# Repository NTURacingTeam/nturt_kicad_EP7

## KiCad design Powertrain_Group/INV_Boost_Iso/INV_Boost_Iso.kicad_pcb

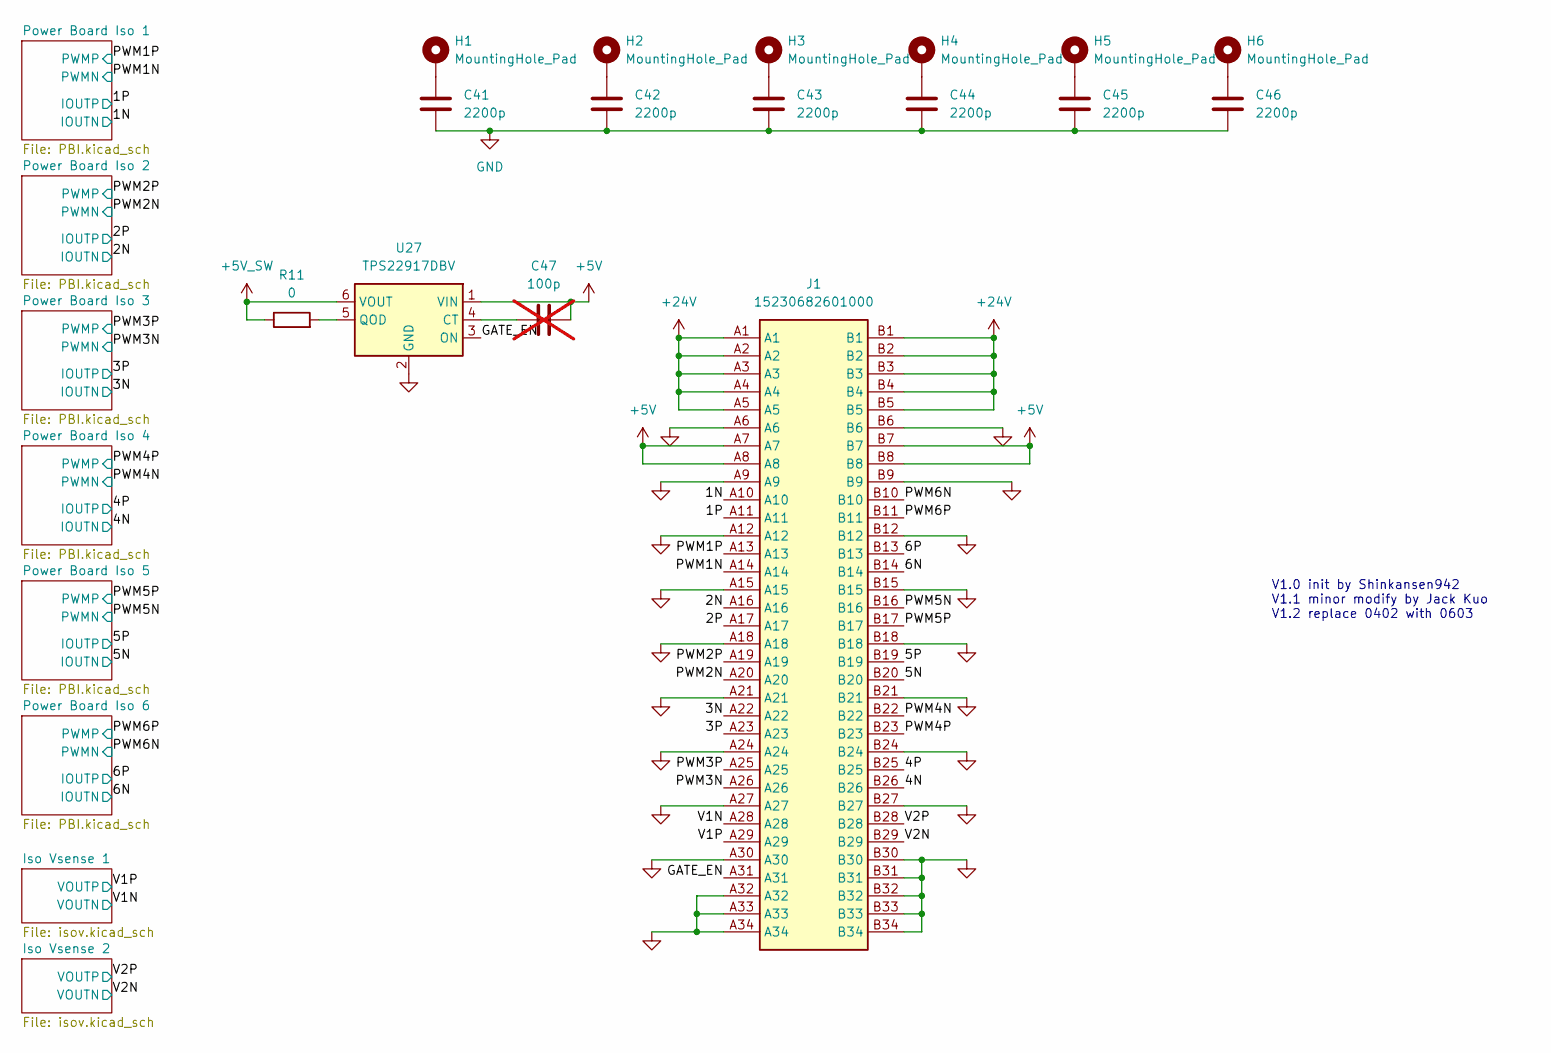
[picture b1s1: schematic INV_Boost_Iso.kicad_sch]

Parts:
C41, C42, C43, C44, C45, C46: 2200p; C_8060_Murata_DK1
C47: 100p; C_0402_1005Metric; not fitted
H1, H2, H3, H4, H5, H6: MountingHole_Pad; MountingHole_4.3mm_M4_Pad_Via
J1: 15230682601000; HARTING 15230682601000; Manufacturer_Part_Number 15230682601000; Mouser Part Number 617-15230682601000
R11: 0; R_0402_1005Metric
U27: TPS22917DBV; SOT-23-6

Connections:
+5V: C47.2, J1.A7, J1.A8, J1.B7, J1.B8, U27.1 (VIN); also elsewhere on the board
+5V_SW: R11.1, U27.6 (VOUT); also elsewhere on the board
+24V: J1.A1, J1.A2, J1.A3, J1.A4, J1.A5, J1.B1, J1.B2, J1.B3, J1.B4, J1.B5; also elsewhere on the board
/1N: J1.A10; also elsewhere on the board
/1P: J1.A11; also elsewhere on the board
/2N: J1.A16; also elsewhere on the board
/2P: J1.A17; also elsewhere on the board
/3N: J1.A22; also elsewhere on the board
/3P: J1.A23; also elsewhere on the board
/4N: J1.B26; also elsewhere on the board
/4P: J1.B25; also elsewhere on the board
/5N: J1.B20; also elsewhere on the board
/5P: J1.B19; also elsewhere on the board
/6N: J1.B14; also elsewhere on the board
/6P: J1.B13; also elsewhere on the board
/GATE_EN: J1.A31, U27.3 (ON)
/PWM1N: J1.A14; also elsewhere on the board
/PWM1P: J1.A13; also elsewhere on the board
/PWM2N: J1.A20; also elsewhere on the board
/PWM2P: J1.A19; also elsewhere on the board
/PWM3N: J1.A26; also elsewhere on the board
/PWM3P: J1.A25; also elsewhere on the board
/PWM4N: J1.B22; also elsewhere on the board
/PWM4P: J1.B23; also elsewhere on the board
/PWM5N: J1.B16; also elsewhere on the board
/PWM5P: J1.B17; also elsewhere on the board
/PWM6N: J1.B10; also elsewhere on the board
/PWM6P: J1.B11; also elsewhere on the board
/V1N: J1.A28; also elsewhere on the board
/V1P: J1.A29; also elsewhere on the board
/V2N: J1.B29; also elsewhere on the board
/V2P: J1.B28; also elsewhere on the board
GND: C41.1, C42.1, C43.1, C44.1, C45.1, C46.1, J1.A6, J1.A9, J1.A12, J1.A15, J1.A18, J1.A21, J1.A24, J1.A27, J1.A30, J1.A32, J1.A33, J1.A34, J1.B6, J1.B9, J1.B12, J1.B15, J1.B18, J1.B21, J1.B24, J1.B27, J1.B30, J1.B31, J1.B32, J1.B33, J1.B34, U27.2 (GND); also elsewhere on the board
unnamed: C41.2, H1.1
unnamed: C42.2, H2.1
unnamed: C43.2, H3.1
unnamed: C44.2, H4.1
unnamed: C45.2, H5.1
unnamed: C46.2, H6.1
unnamed: C47.1, U27.4 (CT)
unnamed: R11.2, U27.5 (QOD)

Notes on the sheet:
V1.0 init by Shinkansen942 V1.1 minor modify by Jack Kuo V1.2 replace 0402 with 0603

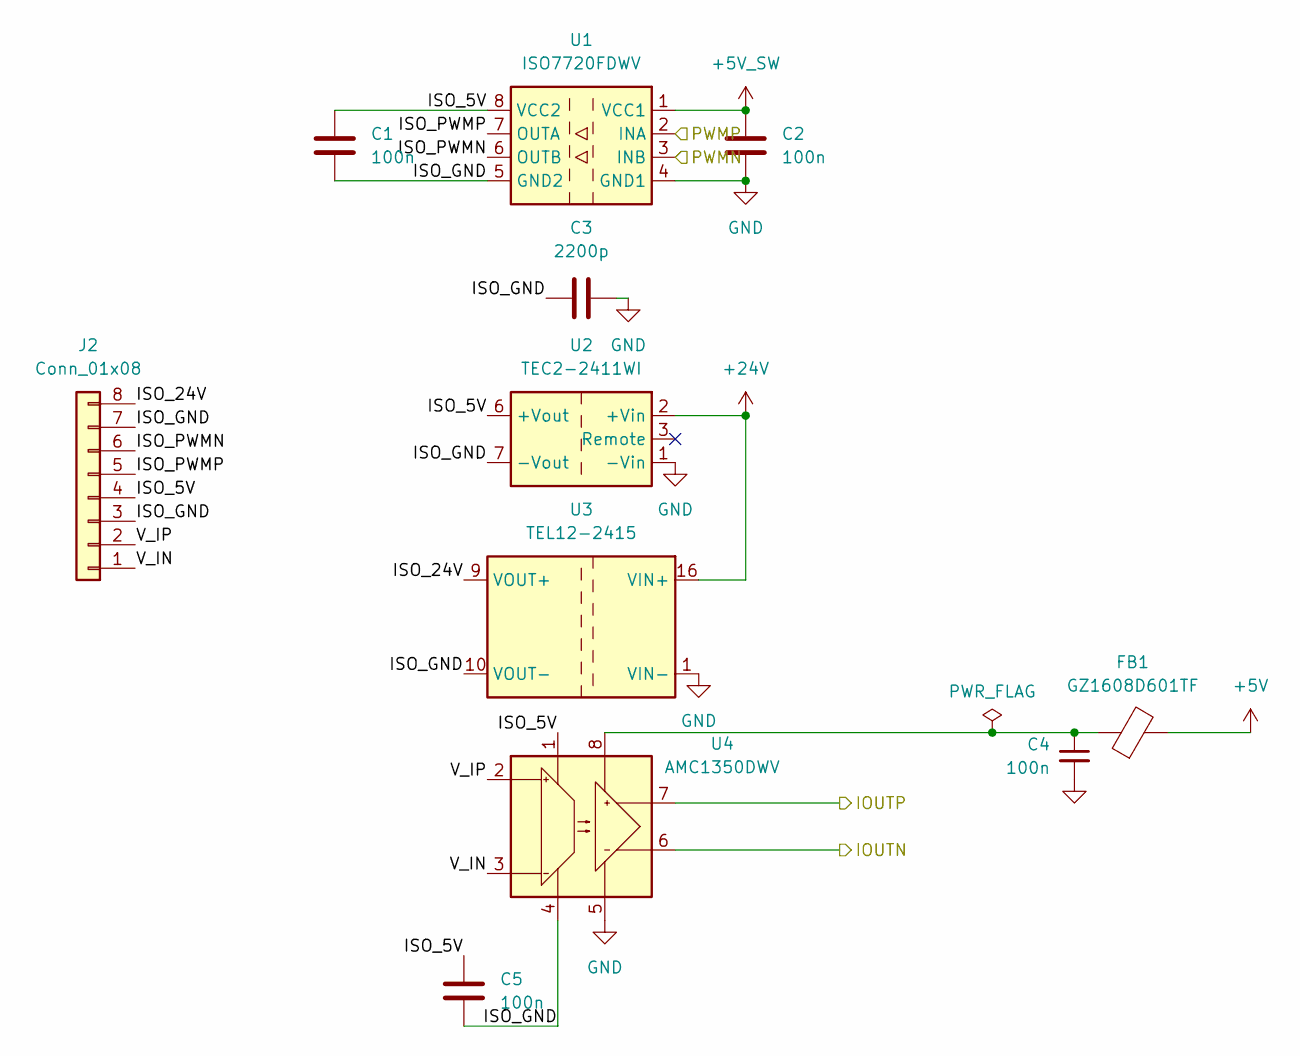
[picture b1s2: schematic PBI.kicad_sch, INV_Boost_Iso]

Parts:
C1, C2, C4, C5: 100n; C_0603_1608Metric
C3: 2200p; C_8060_Murata_DK1
FB1: GZ1608D601TF; C_0603_1608Metric
J2: Conn_01x08; JST_XA_S08B-XASK-1_1x08_P2.50mm_Horizontal
U1: ISO7720FDWV; SOIC-8_7.5x5.85mm_P1.27mm
U2: TEC2-2411WI; Converter_DCDC_Meanwell_xPx0xW8-xx_THT
U3: TEL12-2415; Converter_DCDC_TRACO_TEL12-xxxx_THT
U4: AMC1350DWV; SOIC-8_7.5x5.85mm_P1.27mm

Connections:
+5V: FB1.2; also elsewhere on the board
+5V_SW: C2.1, U1.1 (VCC1); also elsewhere on the board
+24V: U2.2 (+Vin), U3.16 (VIN+); also elsewhere on the board
/1N: U4.6 (OUT-); also elsewhere on the board
/1P: U4.7 (OUT+); also elsewhere on the board
/PWM1N: U1.3 (INB); also elsewhere on the board
/PWM1P: U1.2 (INA); also elsewhere on the board
/Power Board Iso 1/ISO_5V: C1.1, C5.1, J2.4, U1.8 (VCC2), U2.6 (+Vout), U4.1 (VDD1)
/Power Board Iso 1/ISO_24V: J2.8, U3.9 (VOUT+)
/Power Board Iso 1/ISO_GND: C1.2, C3.1, C5.2, J2.3, J2.7, U1.5 (GND2), U2.7 (-Vout), U3.10 (VOUT-), U4.4 (GND1)
/Power Board Iso 1/ISO_PWMN: J2.6, U1.6 (OUTB)
/Power Board Iso 1/ISO_PWMP: J2.5, U1.7 (OUTA)
/Power Board Iso 1/V_IN: J2.1, U4.3 (IN-)
/Power Board Iso 1/V_IP: J2.2, U4.2 (IN+)
GND: C2.2, C3.2, C4.2, U1.4 (GND1), U2.1 (-Vin), U3.1 (VIN-), U4.5 (GND2); also elsewhere on the board
unnamed: C4.1, FB1.1, U4.8 (VDD2)

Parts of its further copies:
C6, C7, C9, C10, C11, C12, C14, C15, C16, C17, C19, C20, C21, C22, C24, C25, C26, C27, C29, C30: 100n; C_0603_1608Metric
C8, C13, C18, C23, C28: 2200p; C_8060_Murata_DK1
FB2, FB3, FB4, FB5, FB6: GZ1608D601TF; C_0603_1608Metric
J3, J4, J5, J6, J7: Conn_01x08; JST_XA_S08B-XASK-1_1x08_P2.50mm_Horizontal
U5, U9, U13, U17, U21: ISO7720FDWV; SOIC-8_7.5x5.85mm_P1.27mm
U6, U10, U14, U18, U22: TEC2-2411WI; Converter_DCDC_Meanwell_xPx0xW8-xx_THT
U7, U11, U15, U19, U23: TEL12-2415; Converter_DCDC_TRACO_TEL12-xxxx_THT
U8, U12, U16, U20, U24: AMC1350DWV; SOIC-8_7.5x5.85mm_P1.27mm

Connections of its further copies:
+5V: FB2.2, FB3.2, FB4.2, FB5.2, FB6.2; also elsewhere on the board
+5V_SW: C7.1, C12.1, C17.1, C22.1, C27.1, U5.1 (VCC1), U9.1 (VCC1), U13.1 (VCC1), U17.1 (VCC1), U21.1 (VCC1); also elsewhere on the board
+24V: U6.2 (+Vin), U7.16 (VIN+), U10.2 (+Vin), U11.16 (VIN+), U14.2 (+Vin), U15.16 (VIN+), U18.2 (+Vin), U19.16 (VIN+), U22.2 (+Vin), U23.16 (VIN+); also elsewhere on the board
/2N: U8.6 (OUT-); also elsewhere on the board
/2P: U8.7 (OUT+); also elsewhere on the board
/3N: U12.6 (OUT-); also elsewhere on the board
/3P: U12.7 (OUT+); also elsewhere on the board
/4N: U16.6 (OUT-); also elsewhere on the board
/4P: U16.7 (OUT+); also elsewhere on the board
/5N: U20.6 (OUT-); also elsewhere on the board
/5P: U20.7 (OUT+); also elsewhere on the board
/6N: U24.6 (OUT-); also elsewhere on the board
/6P: U24.7 (OUT+); also elsewhere on the board
/PWM2N: U5.3 (INB); also elsewhere on the board
/PWM2P: U5.2 (INA); also elsewhere on the board
/PWM3N: U9.3 (INB); also elsewhere on the board
/PWM3P: U9.2 (INA); also elsewhere on the board
/PWM4N: U13.3 (INB); also elsewhere on the board
/PWM4P: U13.2 (INA); also elsewhere on the board
/PWM5N: U17.3 (INB); also elsewhere on the board
/PWM5P: U17.2 (INA); also elsewhere on the board
/PWM6N: U21.3 (INB); also elsewhere on the board
/PWM6P: U21.2 (INA); also elsewhere on the board
/Power Board Iso 2/ISO_5V: C6.1, C10.1, J3.4, U5.8 (VCC2), U6.6 (+Vout), U8.1 (VDD1)
/Power Board Iso 2/ISO_24V: J3.8, U7.9 (VOUT+)
/Power Board Iso 2/ISO_GND: C6.2, C8.1, C10.2, J3.3, J3.7, U5.5 (GND2), U6.7 (-Vout), U7.10 (VOUT-), U8.4 (GND1)
/Power Board Iso 2/ISO_PWMN: J3.6, U5.6 (OUTB)
/Power Board Iso 2/ISO_PWMP: J3.5, U5.7 (OUTA)
/Power Board Iso 2/V_IN: J3.1, U8.3 (IN-)
/Power Board Iso 2/V_IP: J3.2, U8.2 (IN+)
/Power Board Iso 3/ISO_5V: C11.1, C15.1, J4.4, U9.8 (VCC2), U10.6 (+Vout), U12.1 (VDD1)
/Power Board Iso 3/ISO_24V: J4.8, U11.9 (VOUT+)
/Power Board Iso 3/ISO_GND: C11.2, C13.1, C15.2, J4.3, J4.7, U9.5 (GND2), U10.7 (-Vout), U11.10 (VOUT-), U12.4 (GND1)
/Power Board Iso 3/ISO_PWMN: J4.6, U9.6 (OUTB)
/Power Board Iso 3/ISO_PWMP: J4.5, U9.7 (OUTA)
/Power Board Iso 3/V_IN: J4.1, U12.3 (IN-)
/Power Board Iso 3/V_IP: J4.2, U12.2 (IN+)
/Power Board Iso 4/ISO_5V: C16.1, C20.1, J5.4, U13.8 (VCC2), U14.6 (+Vout), U16.1 (VDD1)
/Power Board Iso 4/ISO_24V: J5.8, U15.9 (VOUT+)
/Power Board Iso 4/ISO_GND: C16.2, C18.1, C20.2, J5.3, J5.7, U13.5 (GND2), U14.7 (-Vout), U15.10 (VOUT-), U16.4 (GND1)
/Power Board Iso 4/ISO_PWMN: J5.6, U13.6 (OUTB)
/Power Board Iso 4/ISO_PWMP: J5.5, U13.7 (OUTA)
/Power Board Iso 4/V_IN: J5.1, U16.3 (IN-)
/Power Board Iso 4/V_IP: J5.2, U16.2 (IN+)
/Power Board Iso 5/ISO_5V: C21.1, C25.1, J6.4, U17.8 (VCC2), U18.6 (+Vout), U20.1 (VDD1)
/Power Board Iso 5/ISO_24V: J6.8, U19.9 (VOUT+)
/Power Board Iso 5/ISO_GND: C21.2, C23.1, C25.2, J6.3, J6.7, U17.5 (GND2), U18.7 (-Vout), U19.10 (VOUT-), U20.4 (GND1)
/Power Board Iso 5/ISO_PWMN: J6.6, U17.6 (OUTB)
/Power Board Iso 5/ISO_PWMP: J6.5, U17.7 (OUTA)
/Power Board Iso 5/V_IN: J6.1, U20.3 (IN-)
/Power Board Iso 5/V_IP: J6.2, U20.2 (IN+)
/Power Board Iso 6/ISO_5V: C26.1, C30.1, J7.4, U21.8 (VCC2), U22.6 (+Vout), U24.1 (VDD1)
/Power Board Iso 6/ISO_24V: J7.8, U23.9 (VOUT+)
/Power Board Iso 6/ISO_GND: C26.2, C28.1, C30.2, J7.3, J7.7, U21.5 (GND2), U22.7 (-Vout), U23.10 (VOUT-), U24.4 (GND1)
/Power Board Iso 6/ISO_PWMN: J7.6, U21.6 (OUTB)
/Power Board Iso 6/ISO_PWMP: J7.5, U21.7 (OUTA)
/Power Board Iso 6/V_IN: J7.1, U24.3 (IN-)
/Power Board Iso 6/V_IP: J7.2, U24.2 (IN+)
GND: C7.2, C8.2, C9.2, C12.2, C13.2, C14.2, C17.2, C18.2, C19.2, C22.2, C23.2, C24.2, C27.2, C28.2, C29.2, U5.4 (GND1), U6.1 (-Vin), U7.1 (VIN-), U8.5 (GND2), U9.4 (GND1), U10.1 (-Vin), U11.1 (VIN-), U12.5 (GND2), U13.4 (GND1), U14.1 (-Vin), U15.1 (VIN-), U16.5 (GND2), U17.4 (GND1), U18.1 (-Vin), U19.1 (VIN-), U20.5 (GND2), U21.4 (GND1), U22.1 (-Vin), U23.1 (VIN-), U24.5 (GND2); also elsewhere on the board
unnamed: C9.1, FB2.1, U8.8 (VDD2)
unnamed: C14.1, FB3.1, U12.8 (VDD2)
unnamed: C19.1, FB4.1, U16.8 (VDD2)
unnamed: C24.1, FB5.1, U20.8 (VDD2)
unnamed: C29.1, FB6.1, U24.8 (VDD2)

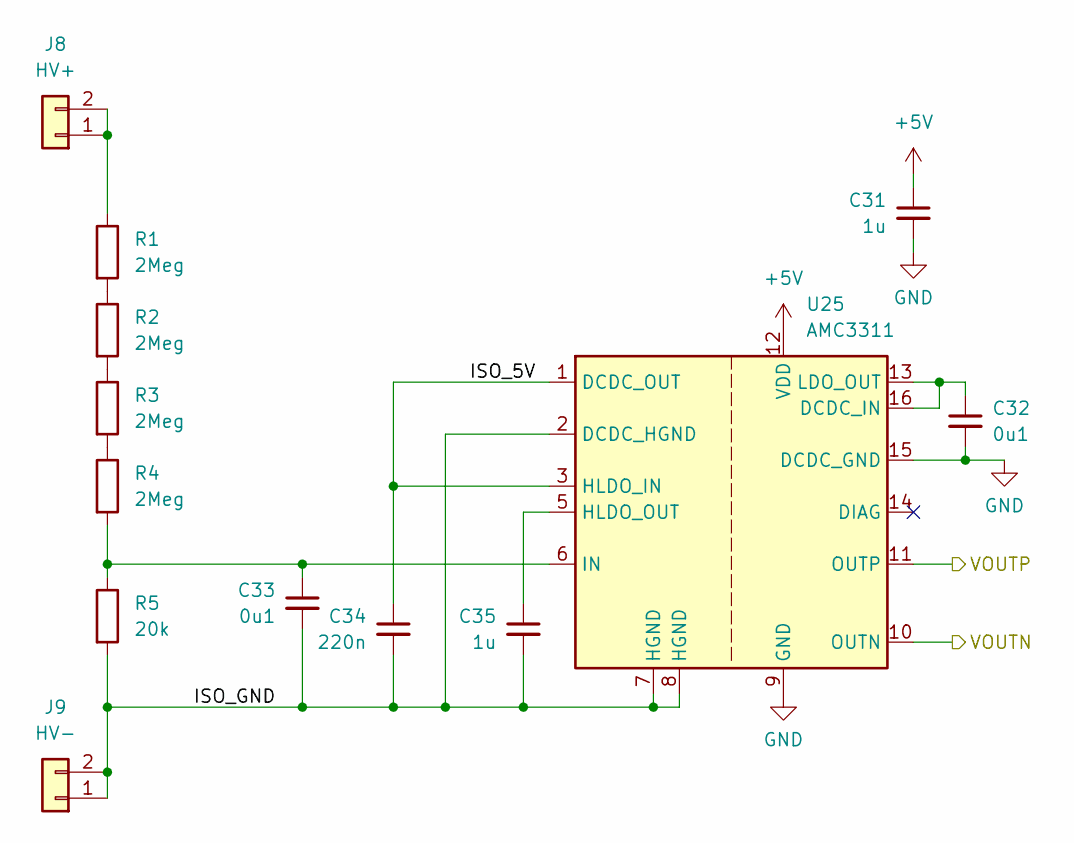
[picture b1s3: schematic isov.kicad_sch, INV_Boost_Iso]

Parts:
C31, C35: 1u; C_0603_1608Metric
C32, C33: 0u1; C_0603_1608Metric
C34: 220n; C_0603_1608Metric
J8: HV+; JST_XA_S02B-XASK-1_1x02_P2.50mm_Horizontal
J9: HV-; JST_XA_S02B-XASK-1_1x02_P2.50mm_Horizontal
R1, R2, R3, R4: 2Meg; R_1206_3216Metric
R5: 20k; R_1206_3216Metric
U25: AMC3311; SOIC-16W_7.5x10.3mm_P1.27mm

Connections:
+5V: C31.1, U25.12 (VDD); also elsewhere on the board
/Iso Vsense 1/ISO_5V: C34.1, U25.1 (DCDC_OUT), U25.3 (HLDO_IN)
/Iso Vsense 1/ISO_GND: C33.2, C34.2, C35.2, J9.1, J9.2, R5.2, U25.2 (DCDC_HGND), U25.7 (HGND), U25.8 (HGND)
/V1N: U25.10 (OUTN); also elsewhere on the board
/V1P: U25.11 (OUTP); also elsewhere on the board
GND: C31.2, C32.2, U25.9 (GND), U25.15 (DCDC_GND); also elsewhere on the board
unnamed: J8.1, J8.2, R1.1
unnamed: R1.2, R2.1
unnamed: R2.2, R3.1
unnamed: R3.2, R4.1
unnamed: C32.1, U25.13 (LDO_OUT), U25.16 (DCDC_IN)
unnamed: C35.1, U25.5 (HLDO_OUT)
unnamed: C33.1, R4.2, R5.1, U25.6 (IN)

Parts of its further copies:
C36, C40: 1u; C_0603_1608Metric
C37, C38: 0u1; C_0603_1608Metric
C39: 220n; C_0603_1608Metric
J10: HV+; JST_XA_S02B-XASK-1_1x02_P2.50mm_Horizontal
J11: HV-; JST_XA_S02B-XASK-1_1x02_P2.50mm_Horizontal
R6, R7, R8, R9: 2Meg; R_1206_3216Metric
R10: 20k; R_1206_3216Metric
U26: AMC3311; SOIC-16W_7.5x10.3mm_P1.27mm

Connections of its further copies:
+5V: C36.1, U26.12 (VDD); also elsewhere on the board
/Iso Vsense 2/ISO_5V: C39.1, U26.1 (DCDC_OUT), U26.3 (HLDO_IN)
/Iso Vsense 2/ISO_GND: C38.2, C39.2, C40.2, J11.1, J11.2, R10.2, U26.2 (DCDC_HGND), U26.7 (HGND), U26.8 (HGND)
/V2N: U26.10 (OUTN); also elsewhere on the board
/V2P: U26.11 (OUTP); also elsewhere on the board
GND: C36.2, C37.2, U26.9 (GND), U26.15 (DCDC_GND); also elsewhere on the board
unnamed: J10.1, J10.2, R6.1
unnamed: R6.2, R7.1
unnamed: R7.2, R8.1
unnamed: R8.2, R9.1
unnamed: C37.1, U26.13 (LDO_OUT), U26.16 (DCDC_IN)
unnamed: C40.1, U26.5 (HLDO_OUT)
unnamed: C38.1, R9.2, R10.1, U26.6 (IN)

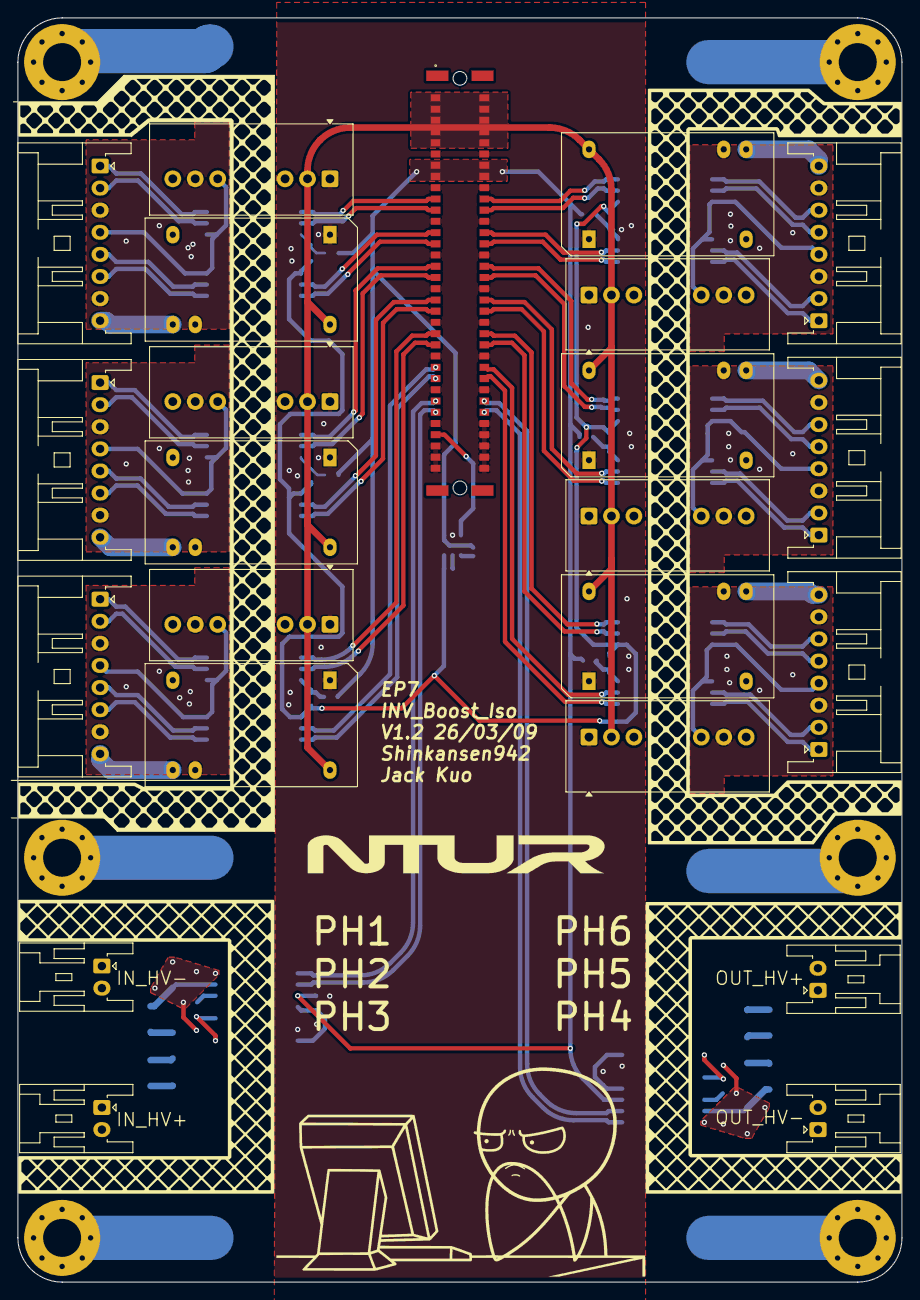
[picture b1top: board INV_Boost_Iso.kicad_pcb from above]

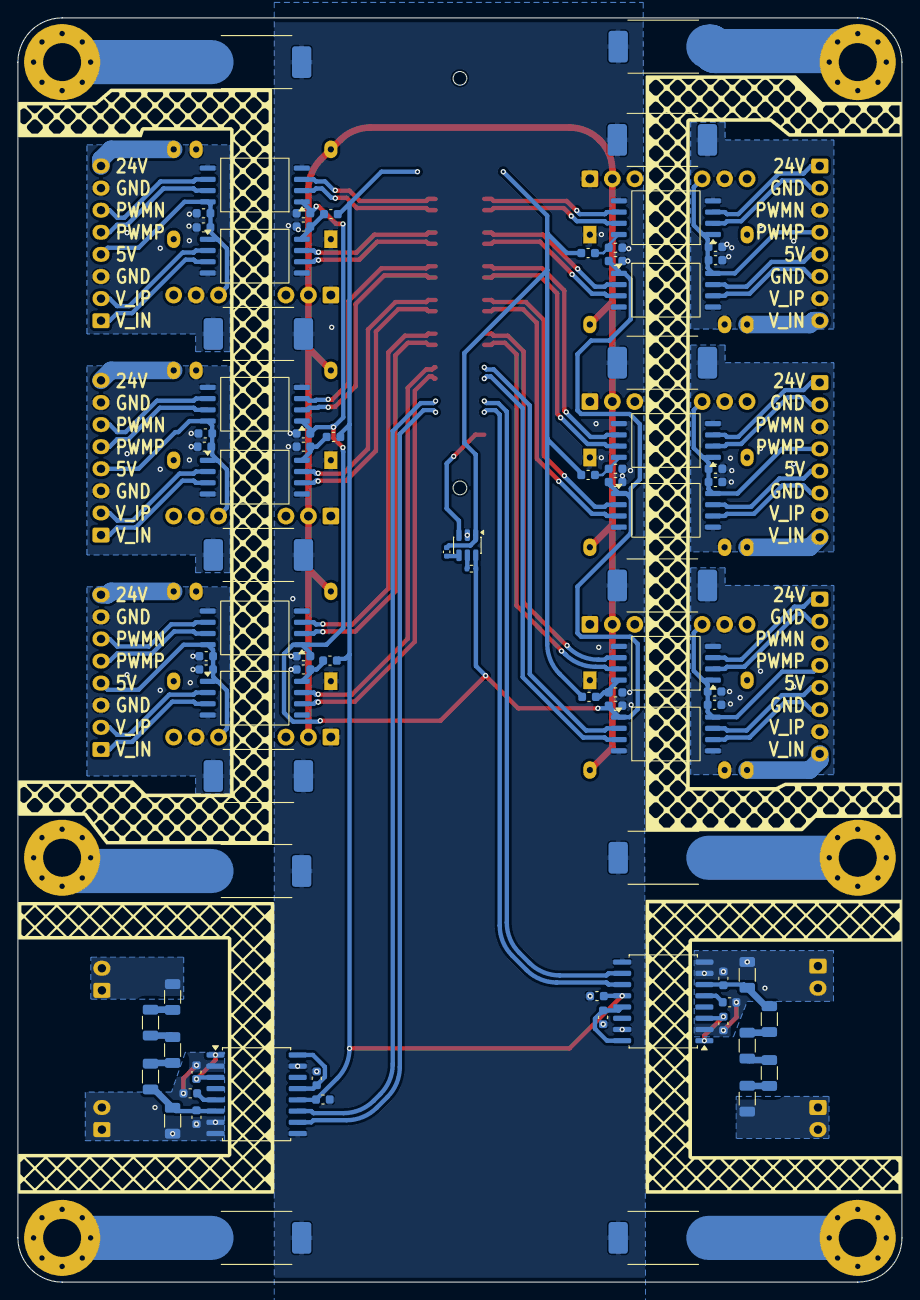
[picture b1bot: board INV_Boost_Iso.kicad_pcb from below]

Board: 2 copper layers, 100.0 x 143.0 mm, 108 parts (79 on the bottom side), 107 nets.

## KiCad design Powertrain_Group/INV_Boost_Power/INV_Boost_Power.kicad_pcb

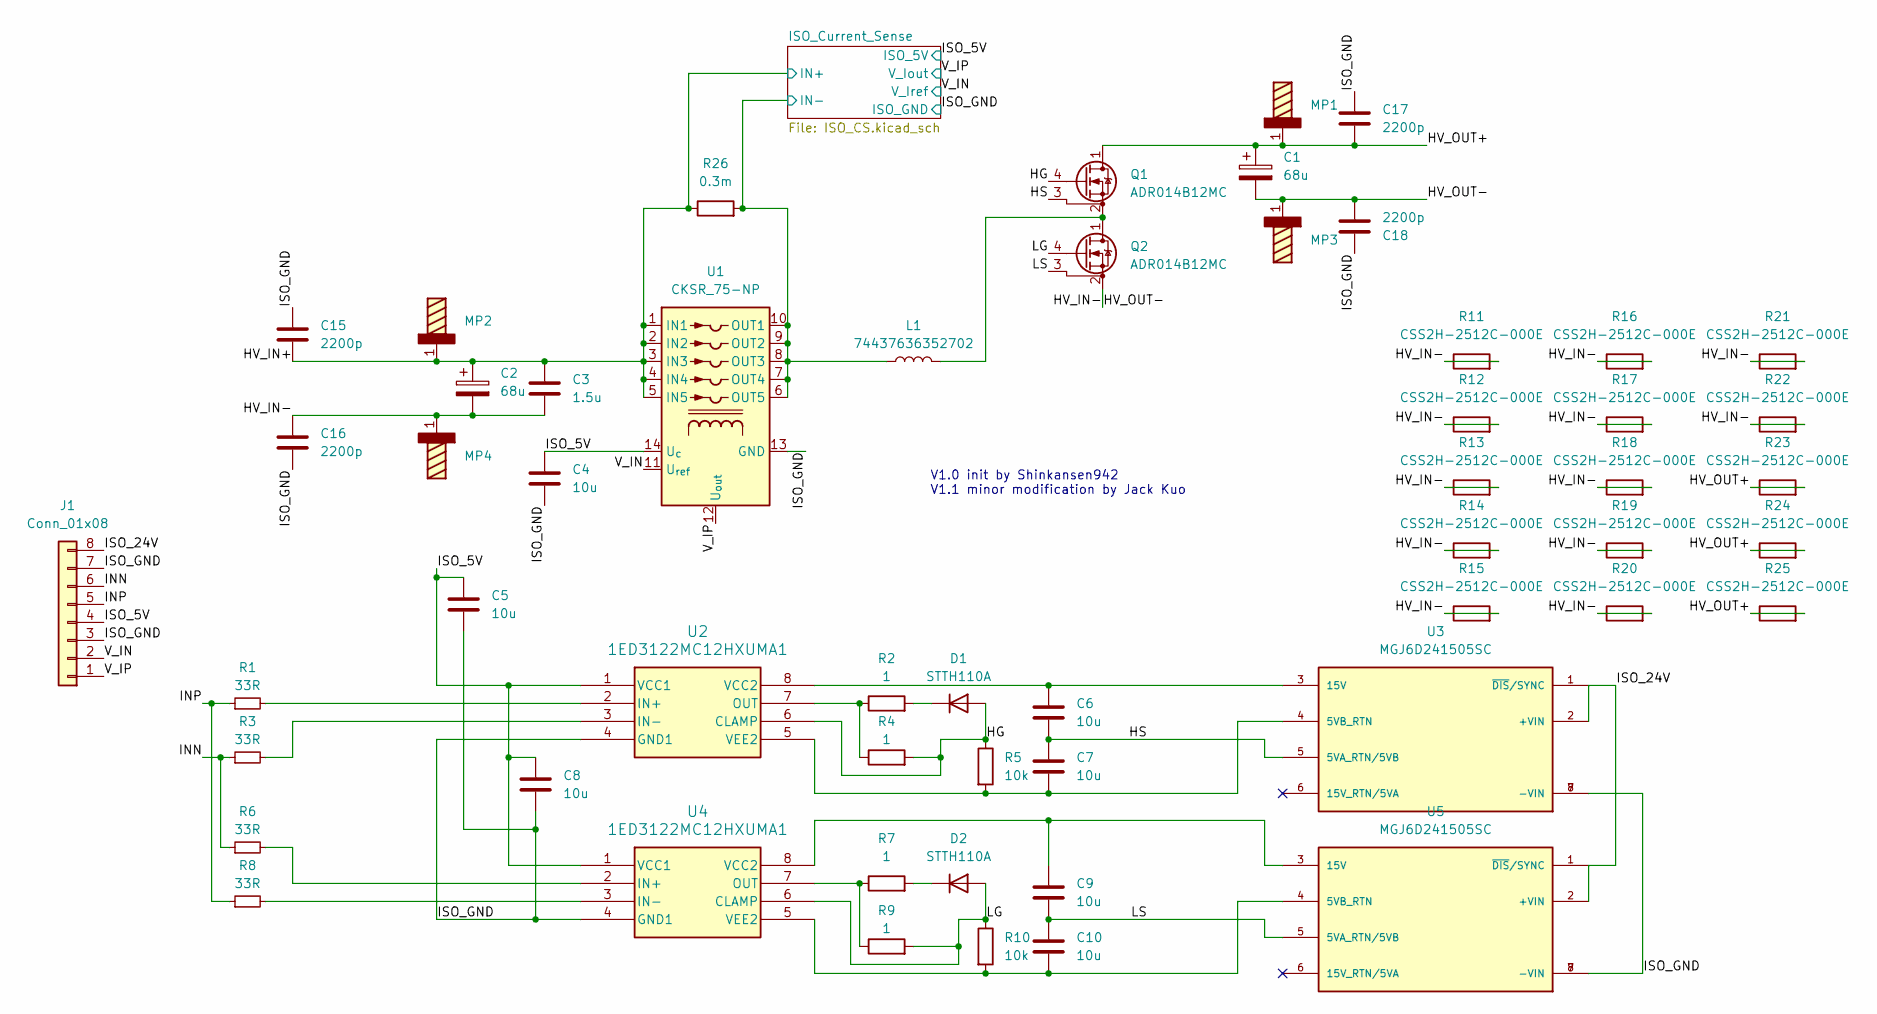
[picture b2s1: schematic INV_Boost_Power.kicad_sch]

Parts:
C1, C2: 68u; CP_Radial_D25.0mm_P10.00mm_SnapIn
C3: 1.5u; TKD_CeraLink_FA3
C4, C5, C6, C7, C8, C9, C10: 10u; C_0805_2012Metric
C15, C16, C17, C18: 2200p; C_8060_Murata_DK1
D1, D2: STTH110A; D_SMA
J1: Conn_01x08; JST_XA_B08B-XASK-1_1x08_P2.50mm_Vertical
L1: 74437636352702; L_Wurth_WE-HCFT-3635_74437636352702
MP1, MP2, MP3, MP4: 74651175R; MP_Wurth_WP-THRSH_74651175R; Part Number 74651175R
Q1, Q2: ADR014B12MC; TO-247-4_Horizontal_TabUp_NoHole
R1, R3, R6, R8: 33R; R_0805_2012Metric
R2, R4, R7, R9: 1; R_2010_5025Metric
R5, R10: 10k; R_1206_3216Metric
R11, R12, R13, R14, R15, R16, R17, R18, R19, R20, R21, R22, R23, R24, R25: CSS2H-2512C-000E; R_2512_6332Metric
R26: 0.3m; R_4020_10251Metric
U1: CKSR_75-NP; LEM_CKSR
U2, U4: 1ED3122MC12HXUMA1; Infineon_PG-DSO-8-59_7.5x6.3mm
U3, U5: MGJ6D241505SC; Murata_PMPN

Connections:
/HG: D1.2 (A), Q1.4 (G), R4.2, R5.1, U2.6 (CLAMP)
/HS: C6.2, C7.1, Q1.3 (DS), U3.5 (5VA_RTN/5VB)
/HV_IN+: C2.1, C3.1, C15.2, MP2.1, R26.1, U1.1 (IN1), U1.2 (IN2), U1.3 (IN3), U1.4 (IN4), U1.5 (IN5); also elsewhere on the board
/HV_IN-: C1.2, C2.2, C3.2, C16.1, C18.2, MP3.1, MP4.1, Q2.2 (S), R11.1, R11.2, R12.1, R12.2, R13.1, R13.2, R14.1, R14.2, R15.1, R15.2, R16.1, R16.2, R17.1, R17.2, R18.1, R18.2, R19.1, R19.2, R20.1, R20.2, R21.1, R21.2, R22.1, R22.2
/HV_OUT+: C1.1, C17.2, MP1.1, Q1.1 (D), R23.1, R23.2, R24.1, R24.2, R25.1, R25.2
/INN: J1.6, R3.1, R6.1
/INP: J1.5, R1.1, R8.1
/ISO_5V: C4.1, C5.1, C8.1, J1.4, U1.14 (U_{c}), U2.1 (VCC1), U4.1 (VCC1); also elsewhere on the board
/ISO_24V: J1.8, U3.1 (~DIS/SYNC), U3.2 (+VIN), U5.1 (~DIS/SYNC), U5.2 (+VIN)
/ISO_Current_Sense/IN-: L1.1, R26.2, U1.6 (OUT5), U1.7 (OUT4), U1.8 (OUT3), U1.9 (OUT2), U1.10 (OUT1); also elsewhere on the board
/ISO_GND: C4.2, C5.2, C8.2, C15.1, C16.2, C17.1, C18.1, J1.3, J1.7, U1.13 (GND), U2.4 (GND1), U3.7 (-VIN), U3.8 (-VIN), U4.4 (GND1), U5.7 (-VIN), U5.8 (-VIN); also elsewhere on the board
/LG: D2.2 (A), Q2.4 (G), R9.2, R10.1, U4.6 (CLAMP)
/LS: C9.2, C10.1, Q2.3 (DS), U5.5 (5VA_RTN/5VB)
/V_IN: J1.2, U1.11 (U_{ref}); also elsewhere on the board
/V_IP: J1.1, U1.12 (U_{out}); also elsewhere on the board
unnamed: D1.1 (K), R2.2
unnamed: D2.1 (K), R7.2
unnamed: L1.2, Q1.2 (S), Q2.1 (D)
unnamed: R1.2, U2.2 (IN+)
unnamed: R3.2, U2.3 (IN-)
unnamed: R2.1, R4.1, U2.7 (OUT)
unnamed: C6.1, U2.8 (VCC2), U3.3 (15V)
unnamed: C7.2, R5.2, U2.5 (VEE2), U3.4 (5VB_RTN)
unnamed: R6.2, U4.2 (IN+)
unnamed: R8.2, U4.3 (IN-)
unnamed: R7.1, R9.1, U4.7 (OUT)
unnamed: C9.1, U4.8 (VCC2), U5.3 (15V)
unnamed: C10.2, R10.2, U4.5 (VEE2), U5.4 (5VB_RTN)

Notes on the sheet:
V1.0 init by Shinkansen942 V1.1 minor modification by Jack Kuo

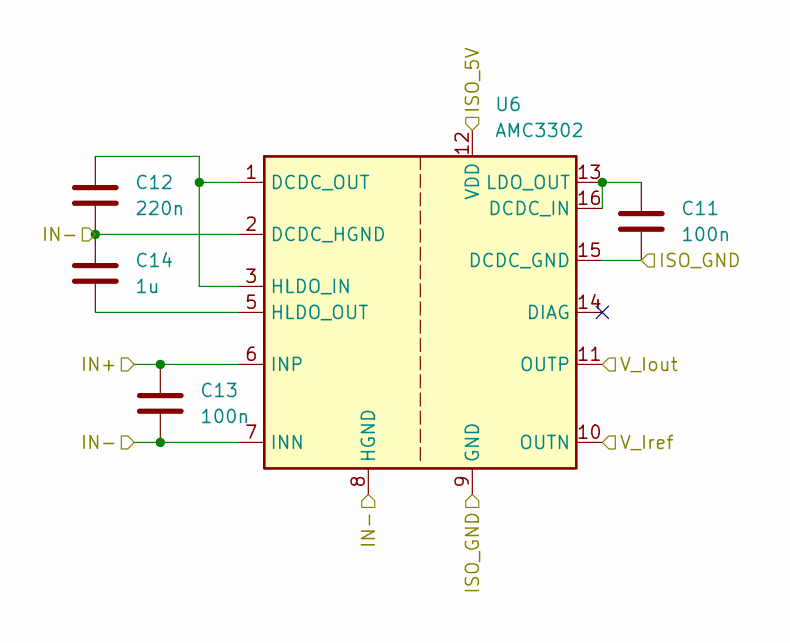
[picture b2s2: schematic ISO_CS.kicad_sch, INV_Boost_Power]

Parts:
C11, C13: 100n; C_0805_2012Metric
C12: 220n; C_0805_2012Metric
C14: 1u; C_0805_2012Metric
U6: AMC3302; SOIC-16W_7.5x10.3mm_P1.27mm

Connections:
/HV_IN+: C13.1, U6.6 (INP); also elsewhere on the board
/ISO_5V: U6.12 (VDD); also elsewhere on the board
/ISO_Current_Sense/IN-: C12.2, C13.2, C14.1, U6.2 (DCDC_HGND), U6.7 (INN), U6.8 (HGND); also elsewhere on the board
/ISO_GND: C11.2, U6.9 (GND), U6.15 (DCDC_GND); also elsewhere on the board
/V_IN: U6.10 (OUTN); also elsewhere on the board
/V_IP: U6.11 (OUTP); also elsewhere on the board
unnamed: C11.1, U6.13 (LDO_OUT), U6.16 (DCDC_IN)
unnamed: C12.1, U6.1 (DCDC_OUT), U6.3 (HLDO_IN)
unnamed: C14.2, U6.5 (HLDO_OUT)

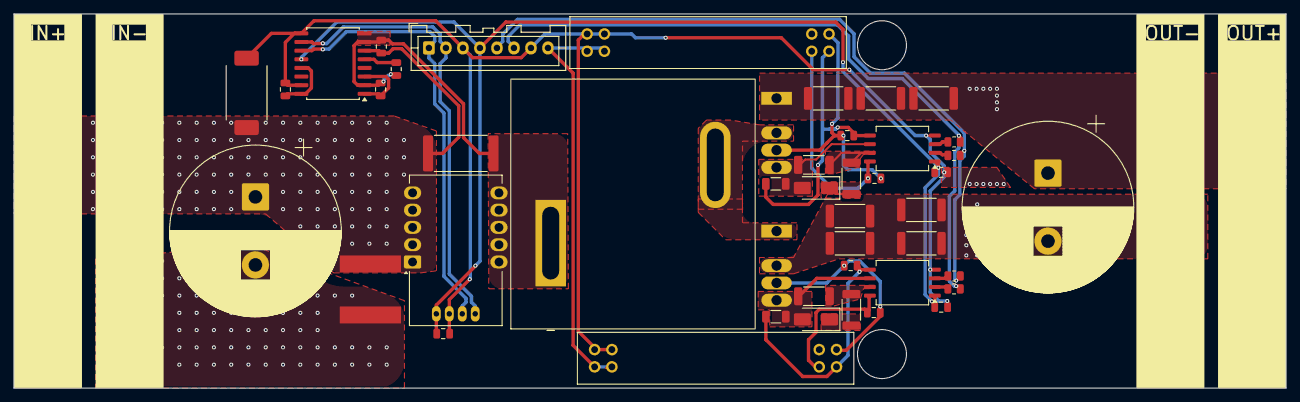
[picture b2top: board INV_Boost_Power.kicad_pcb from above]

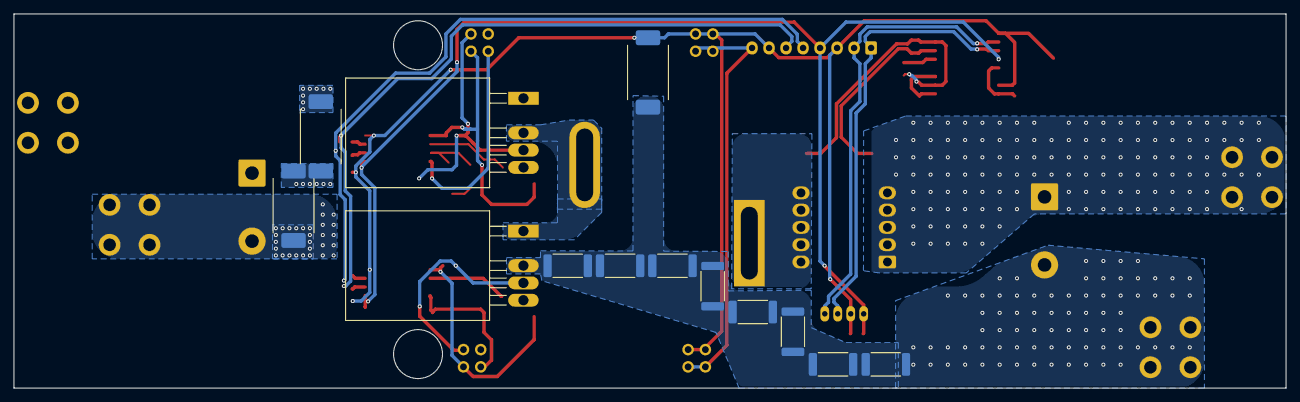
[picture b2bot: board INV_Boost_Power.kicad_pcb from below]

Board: 2 copper layers, 187.0 x 55.0 mm, 60 parts (13 on the bottom side), 31 nets.

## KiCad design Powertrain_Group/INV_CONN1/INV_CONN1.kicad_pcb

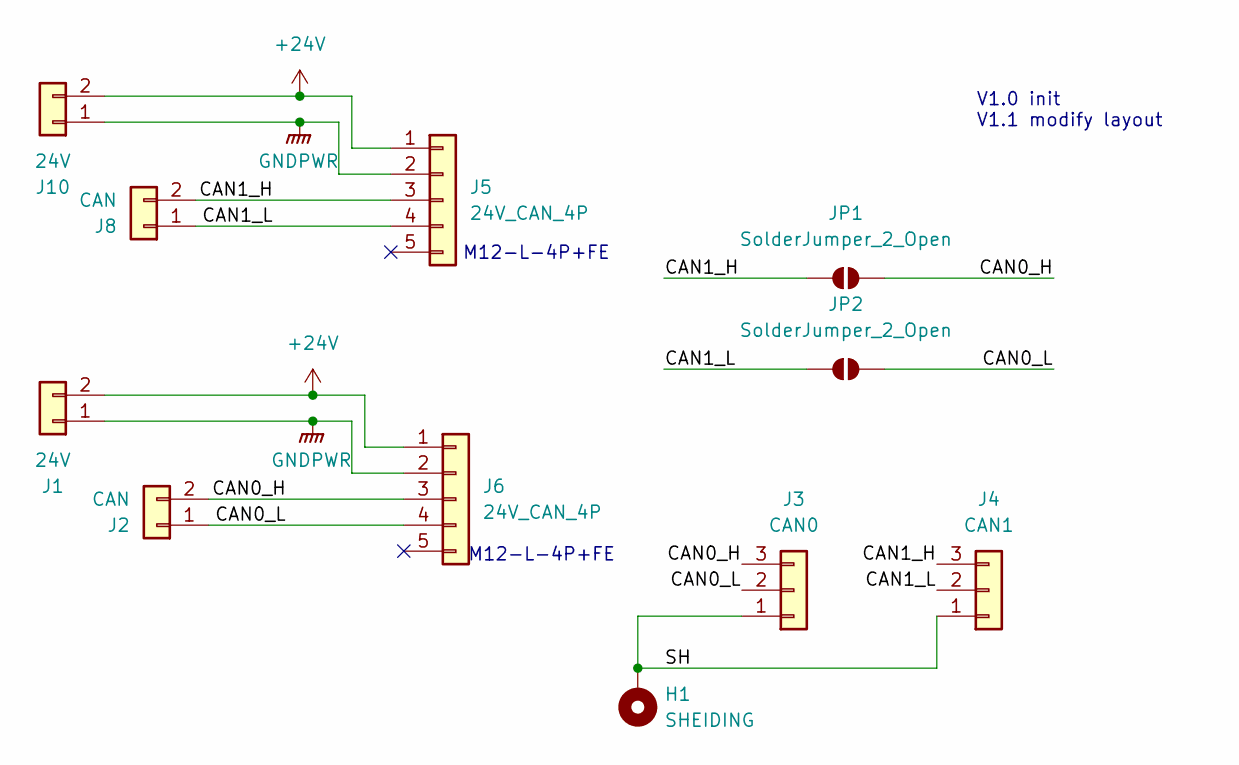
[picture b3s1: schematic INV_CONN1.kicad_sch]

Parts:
H1: SHEIDING; MountingHole_3.2mm_M3_Pad_Via
J1, J10: 24V; JST_VH_B2P-VH_1x02_P3.96mm_Vertical
J2, J8: CAN; JST_XH_B2B-XH-A_1x02_P2.50mm_Vertical
J3: CAN0; JST_XA_B03B-XASK-1_1x03_P2.50mm_Vertical
J4: CAN1; JST_XA_B03B-XASK-1_1x03_P2.50mm_Vertical
J5, J6: 24V_CAN_4P; NianYeong-M12-L-F5P
JP1, JP2: SolderJumper_2_Open; SolderJumper-2_P1.3mm_Open_RoundedPad1.0x1.5mm

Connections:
+24V: J1.2, J5.1, J6.1, J10.2
/CAN0_H: J2.2, J3.3, J6.3, JP1.2 (B)
/CAN0_L: J2.1, J3.2, J6.4, JP2.2 (B)
/CAN1_H: J4.3, J5.3, J8.2, JP1.1 (A)
/CAN1_L: J4.2, J5.4, J8.1, JP2.1 (A)
/SH: H1.1, J3.1, J4.1
GNDPWR: J1.1, J5.2, J6.2, J10.1

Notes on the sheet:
M12-L-4P+FE
V1.0 init V1.1 modify layout

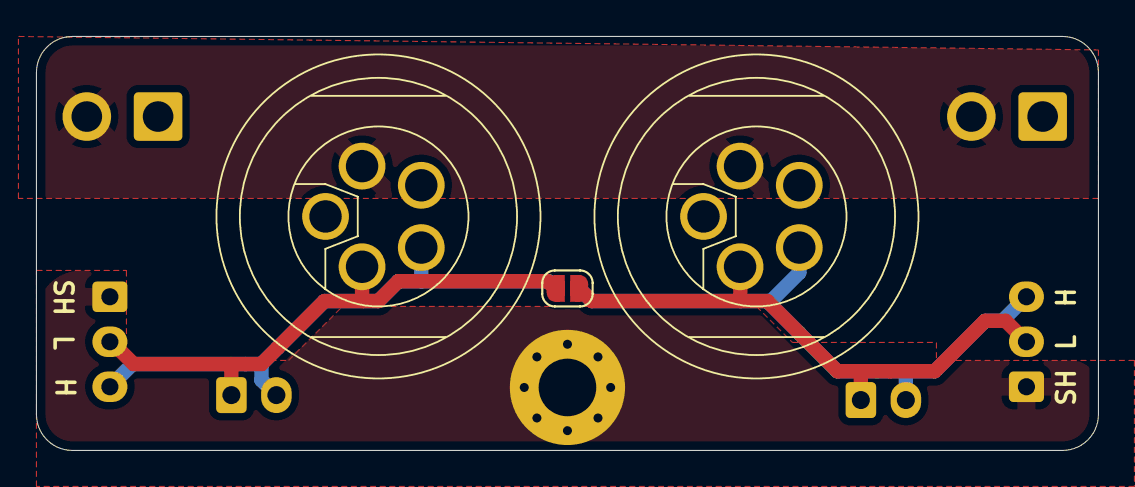
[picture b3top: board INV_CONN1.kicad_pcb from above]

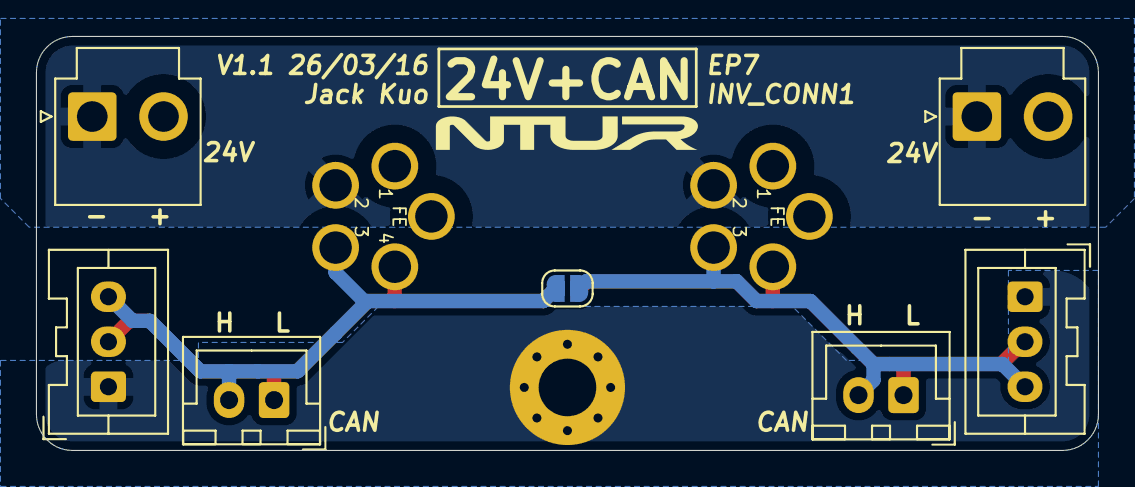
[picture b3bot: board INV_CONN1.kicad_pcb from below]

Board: 2 copper layers, 59.0 x 23.0 mm, 11 parts (7 on the bottom side), 7 nets.

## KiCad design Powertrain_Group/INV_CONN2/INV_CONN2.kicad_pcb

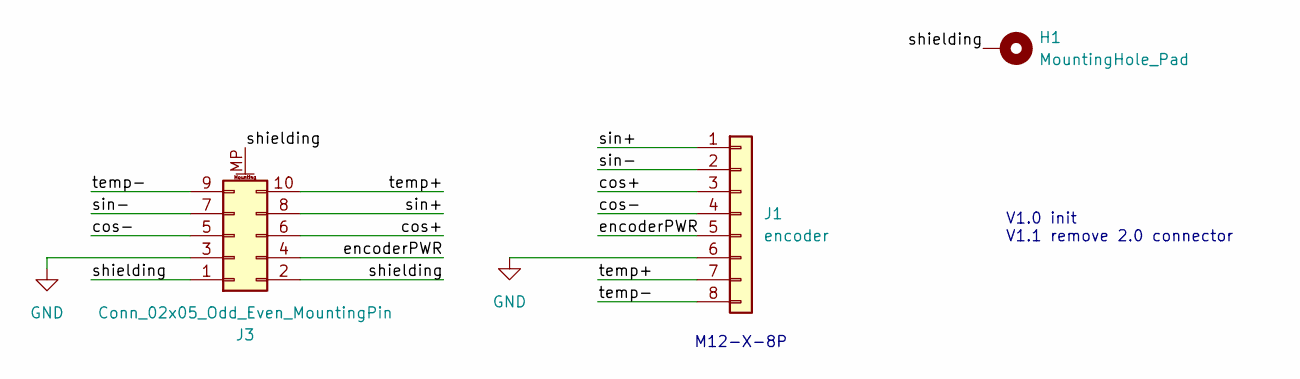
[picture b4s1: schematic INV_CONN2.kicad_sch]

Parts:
H1: MountingHole_Pad; MountingHole_3.2mm_M3_Pad_Via
J1: encoder; NianYeong-M12-X-F4P
J3: Conn_02x05_Odd_Even_MountingPin; CONN_2202010000-SD_10P_MOL

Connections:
/cos+: J1.3, J3.6
/cos-: J1.4, J3.5
/encoderPWR: J1.5, J3.4
/shielding: H1.1, J3.1, J3.2, J3.MP (MountPin)
/sin+: J1.1, J3.8
/sin-: J1.2, J3.7
/temp+: J1.7, J3.10
/temp-: J1.8, J3.9
GND: J1.6, J3.3

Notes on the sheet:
V1.0 init V1.1 remove 2.0 connector
M12-X-8P

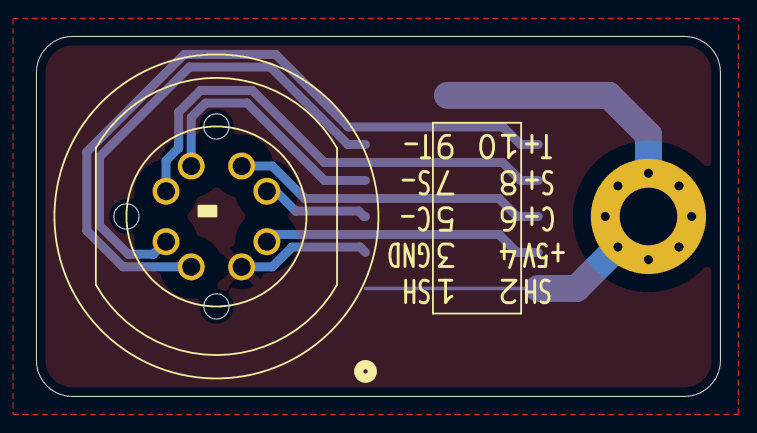
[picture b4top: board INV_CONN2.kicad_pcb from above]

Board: 2 copper layers, 38.0 x 20.0 mm, 3 parts (1 on the bottom side), 9 nets.
